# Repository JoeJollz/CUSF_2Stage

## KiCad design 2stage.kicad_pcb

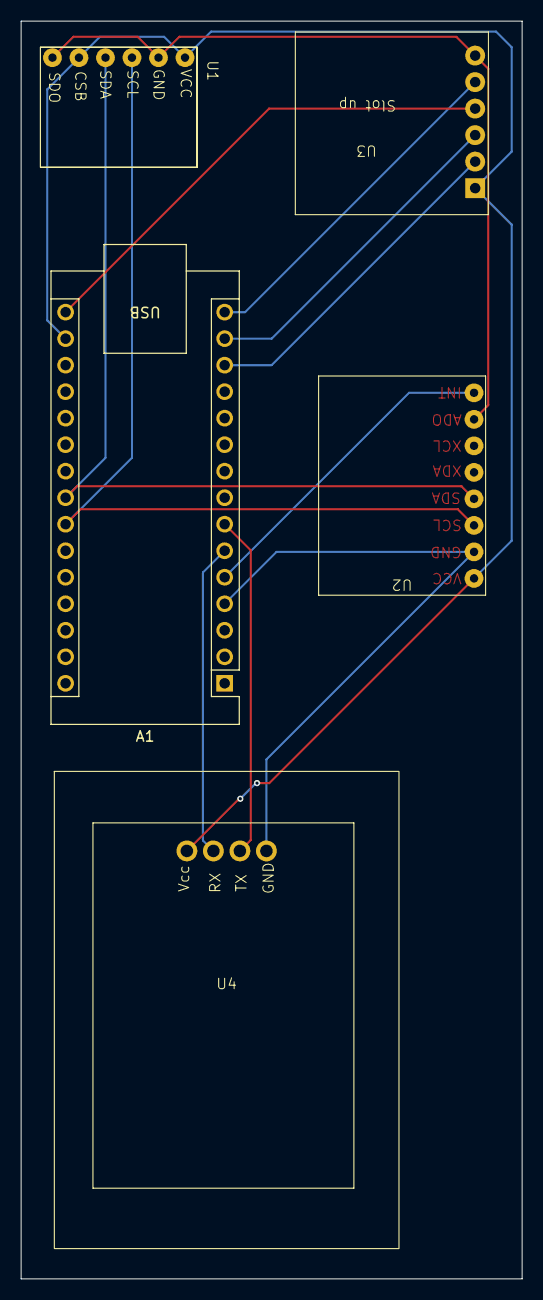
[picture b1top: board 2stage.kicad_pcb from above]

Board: 2 copper layers, 48.0 x 120.5 mm, 5 parts (0 on the bottom side), 11 nets.

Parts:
A1: Arduino_Nano_Every; Arduino_Nano
U1: GY-BMP280
U2: MPU_6050_Hailega_Breakout; MPU_6050_Hailega_breakout_2
U3: MicroSD Reader; MicroSDReader
U4: GY-NEO-M8; GY-NEO-M8N

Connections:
unnamed: A1.17 (3V3), U1.1 (VCC), U1.5 (CSB), U2.1 (VCC), U3.1 (3v3), U4.1 (VCC)
unnamed: A1.5 (D2), U2.8 (INT)
unnamed: A1.6 (D3), U4.2 (RX)
unnamed: A1.7 (D4), U4.3 (TX)
unnamed: A1.13 (D10), U3.2 (CS)
unnamed: A1.15 (MISO), U3.5 (MISO)
unnamed: A1.14 (MOSI), U3.3 (MOSI)
unnamed: A1.16 (SCK), U3.4 (CLK)
unnamed: A1.24 (SCL/A5), U1.3 (SCL), U2.3 (SCL)
unnamed: A1.23 (SDA/A4), U1.4 (SDA), U2.4 (SDA)
unnamed: A1.4 (GND), A1.29 (GND), U1.2 (GND), U1.6 (SDO), U2.2 (GND), U2.7 (ADO), U3.6 (GND), U4.4 (GND)
